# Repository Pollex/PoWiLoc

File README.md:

# PoWiLoc
Pollex' Wireless Locator (PoWi Locator) is a fully Open-Source device used to test LoRaWAN connections and map them on the PoWi website and/or the [TTN Mapper](https://ttnmapper.org/) website.

The locator is designed to be built by everyone who has some technical knowledge (soldering and programming) and the device has several optional features which can be left out to make assembling the device easier.

The hardware is designed in free and Open-Source software called [KiCAD](https://kicad.org/).

The source code for this device is developed in [Visual Studio Code](https://code.visualstudio.com/) (a lightweight editor) with the [PlatformIO](https://platformio.org/) extension. Also both free and Open-Source. This setup is chosen instead of the Arduino IDE because it allows  for cleaner code and better library management.

## This project is in active development and contributions cannot be received at this point in time. As soon as a minimum viable product is built, contributions will open and links to documentation will be provided.

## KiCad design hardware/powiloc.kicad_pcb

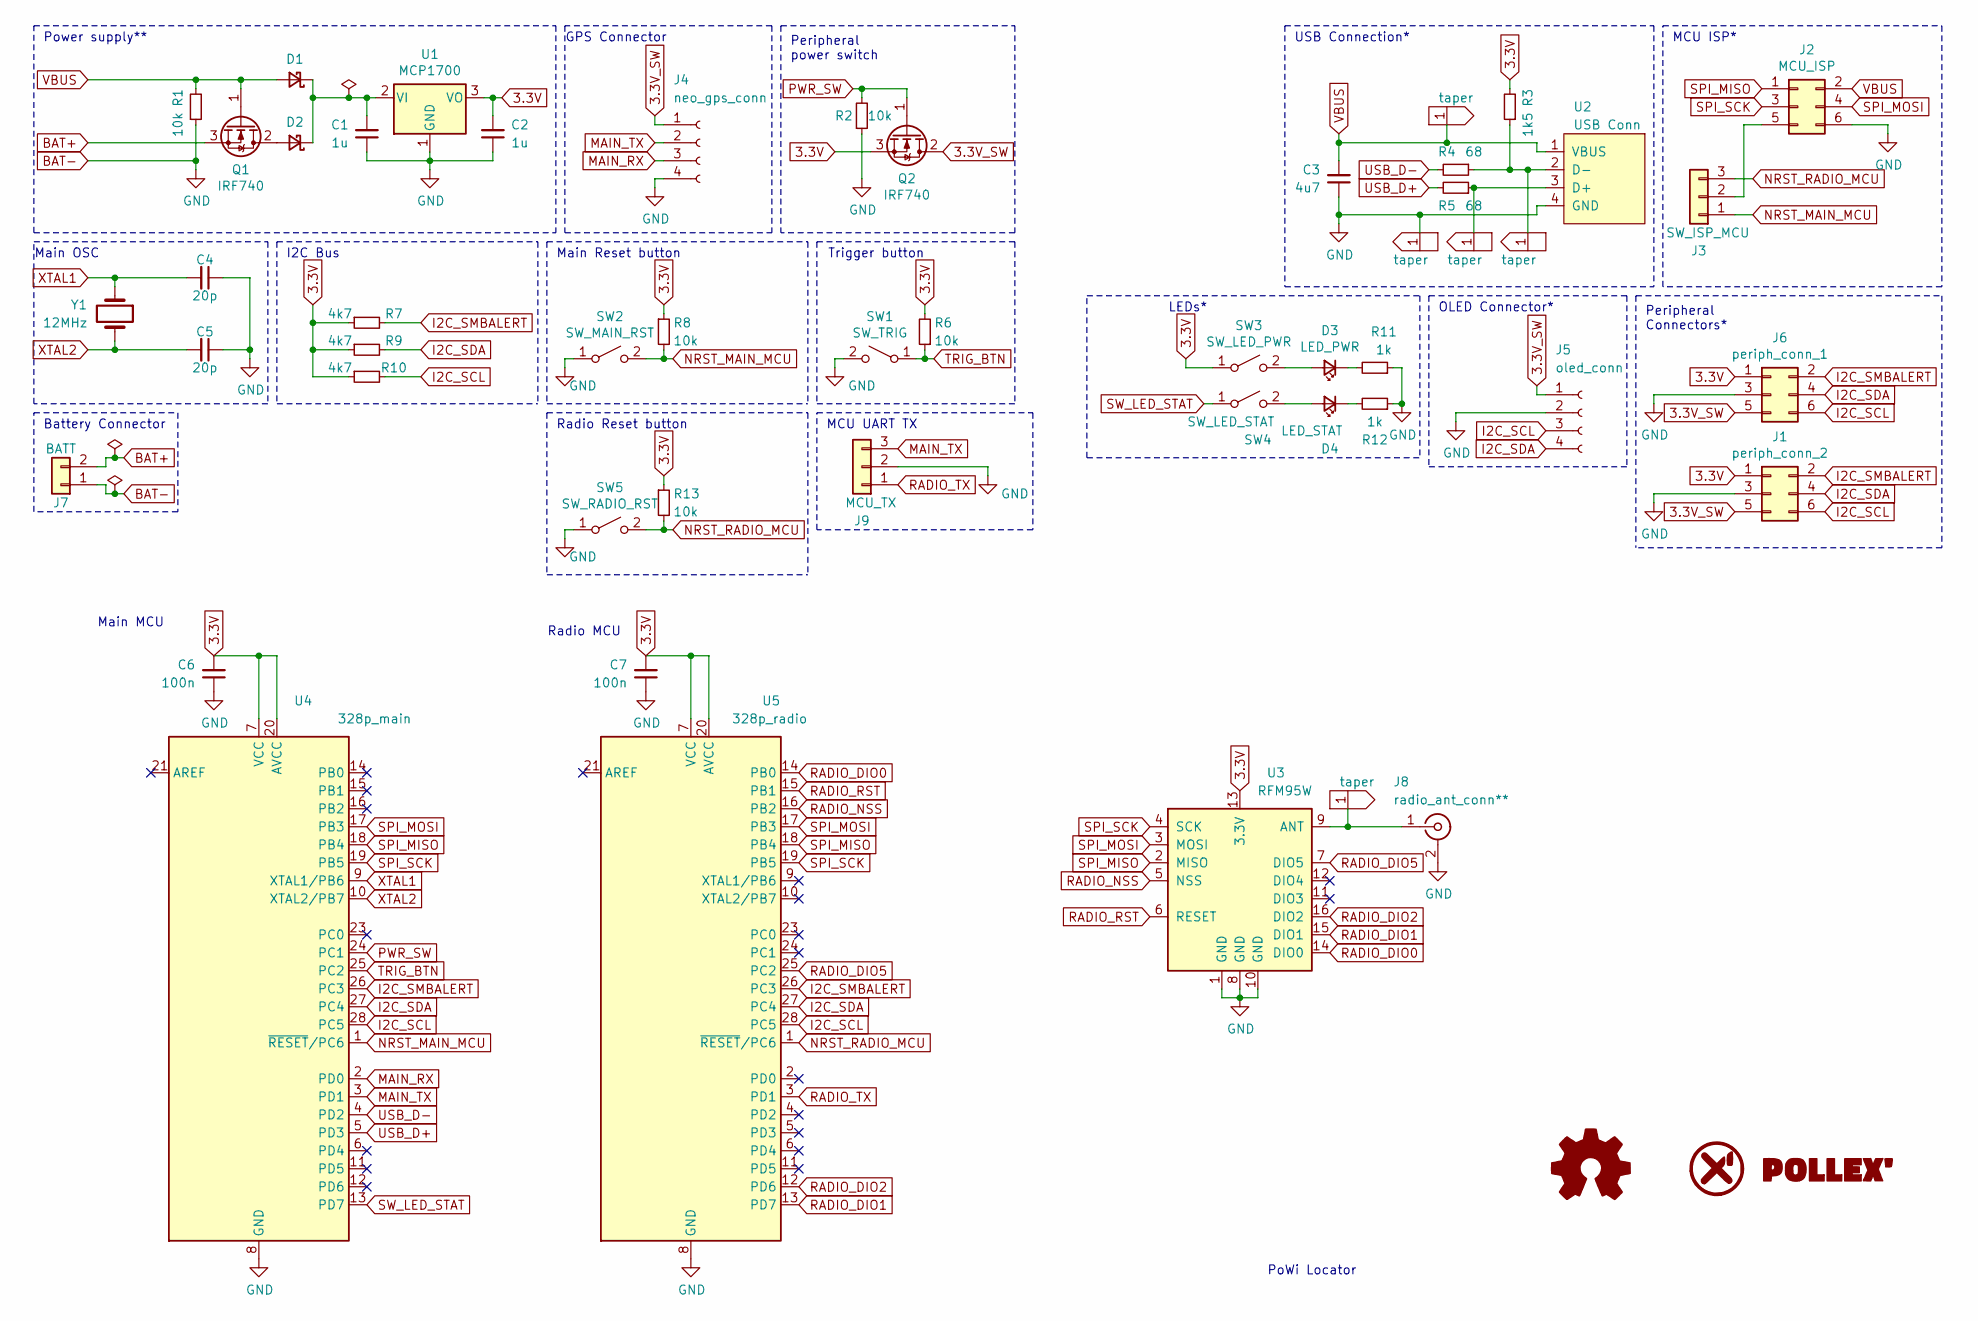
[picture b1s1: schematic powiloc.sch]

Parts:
C1, C2: 1u; C_Disc_D5.0mm_W2.5mm_P5.00mm
C3: 4u7; C_Disc_D5.0mm_W2.5mm_P5.00mm
C4, C5: 20p; C_Disc_D5.0mm_W2.5mm_P2.50mm
C6, C7: 100n; C_Disc_D5.0mm_W2.5mm_P2.50mm
D1, D2: D_Schottky_Small; D_DO-41_SOD81_P7.62mm_Horizontal
D3: LED_PWR; LED_D5.0mm
D4: LED_STAT; LED_D5.0mm
J1: periph_conn_2; PinHeader_2x03_P2.54mm_Vertical
J2: MCU_ISP; PinHeader_2x03_P2.54mm_Vertical
J3: SW_ISP_MCU; PinHeader_1x03_P2.54mm_Vertical
J4: neo_gps_conn; PinSocket_1x04_P2.54mm_Vertical
J5: oled_conn; PinSocket_1x04_P2.54mm_Vertical
J6: periph_conn_1; PinHeader_2x03_P2.54mm_Vertical
J7: BATT; JST_XH_B2B-XH-A_1x02_P2.50mm_Vertical
J8: radio_ant_conn**; SMA_Amphenol_132289_EdgeMount
J9: MCU_TX; PinSocket_1x03_P2.54mm_Vertical
Q1, Q2: IRF740; TO-220-3_Horizontal_TabDown
R1, R2, R6, R8, R13: 10k; R_Axial_DIN0207_L6.3mm_D2.5mm_P7.62mm_Horizontal
R3: 1k5; R_Axial_DIN0207_L6.3mm_D2.5mm_P7.62mm_Horizontal
R4, R5: 68; R_Axial_DIN0207_L6.3mm_D2.5mm_P7.62mm_Horizontal
R7, R9, R10: 4k7; R_Axial_DIN0207_L6.3mm_D2.5mm_P7.62mm_Horizontal
R11, R12: 1k; R_Axial_DIN0207_L6.3mm_D2.5mm_P7.62mm_Horizontal
SW1: SW_TRIG; SW_PUSH_6mm
SW2: SW_MAIN_RST; SW_PUSH_6mm
SW3: SW_LED_PWR; PinHeader_1x02_P2.54mm_Vertical
SW4: SW_LED_STAT; PinHeader_1x02_P2.54mm_Vertical
SW5: SW_RADIO_RST; SW_PUSH_6mm
T1, T2, T5: taper; uwT0.50_0.40_1.00_1.46_1.20
T3, T4: taper; uwT0.50_0.15_1.00_1.24_3.00
U1: MCP1700; TO-92_Inline
U2: USB Conn; USBPCB
U3: RFM95W; HOPERF_RFM9XW_SMD
U4: 328p_main; DIP-28_W7.62mm_Socket
U5: 328p_radio; DIP-28_W7.62mm_Socket
Y1: 12MHz; Crystal_HC49-U_Vertical

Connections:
3.3V: C2.2, C6.2, C7.2, J1.1, J6.1, Q2.3 (S), R3.2, R6.2, R7.1, R8.1, R9.1, R10.1, R13.1, SW3.1 (A), U1.3 (VO), U3.13 (3.3V), U4.7 (VCC), U4.20 (AVCC), U5.7 (VCC), U5.20 (AVCC)
3.3V_SW: J1.5, J4.1, J5.1, J6.5, Q2.2 (D)
BAT+: J7.2, Q1.3 (S)
BAT-: C1.1, C2.1, C3.1, C4.1, C5.1, C6.1, C7.1, J1.3, J2.6, J4.4, J5.2, J6.3, J7.1, J8.2 (Ext), J9.2, R1.1, R2.1, R11.1, R12.1, SW1.2 (B), SW2.1 (A), SW5.1 (A), T2.1, U1.1 (GND), U2.4 (GND), U3.1 (GND), U3.8 (GND), U3.10 (GND), U4.8 (GND), U4.22 (GND), U5.8 (GND), U5.22 (GND)
I2C_SCL: J1.6, J5.3, J6.6, R10.2, U4.28 (PC5), U5.28 (PC5)
I2C_SDA: J1.4, J5.4, J6.4, R9.2, U4.27 (PC4), U5.27 (PC4)
I2C_SMBALERT: J1.2, J6.2, R7.2, U4.26 (PC3), U5.26 (PC3)
MAIN_RX: J4.3, U4.2 (PD0)
MAIN_TX: J4.2, J9.3, U4.3 (PD1)
NRST_MAIN_MCU: J3.1, R8.2, SW2.2 (B), U4.1 (~RESET~/PC6)
NRST_RADIO_MCU: J3.3, R13.2, SW5.2 (B), U5.1 (~RESET~/PC6)
unnamed: C1.2, D1.1 (K), D2.1 (K), U1.2 (VI)
unnamed: D2.2 (A), Q1.2 (D)
unnamed: D3.1 (K), R11.2
unnamed: D3.2 (A), SW3.2 (B)
unnamed: D4.1 (K), R12.2
unnamed: D4.2 (A), SW4.2 (B)
unnamed: J2.5, J3.2
unnamed: J8.1 (In), T5.1, U3.9 (ANT)
unnamed: R3.1, R4.1, T4.1, U2.2 (D-)
unnamed: R5.1, T3.1, U2.3 (D+)
PWR_SW: Q2.1 (G), R2.2, U4.24 (PC1)
RADIO_DIO0: U3.14 (DIO0), U5.14 (PB0)
RADIO_DIO1: U3.15 (DIO1), U5.13 (PD7)
RADIO_DIO2: U3.16 (DIO2), U5.12 (PD6)
RADIO_DIO5: U3.7 (DIO5), U5.25 (PC2)
RADIO_NSS: U3.5 (NSS), U5.16 (PB2)
RADIO_RST: U3.6 (RESET), U5.15 (PB1)
RADIO_TX: J9.1, U5.3 (PD1)
SPI_MISO: J2.1, U3.2 (MISO), U4.18 (PB4), U5.18 (PB4)
SPI_MOSI: J2.4, U3.3 (MOSI), U4.17 (PB3), U5.17 (PB3)
SPI_SCK: J2.3, U3.4 (SCK), U4.19 (PB5), U5.19 (PB5)
SW_LED_STAT: SW4.1 (A), U4.13 (PD7)
TRIG_BTN: R6.1, SW1.1 (A), U4.25 (PC2)
USB_D+: R5.2, U4.5 (PD3)
USB_D-: R4.2, U4.4 (PD2)
VBUS: C3.2, D1.2 (A), J2.2, Q1.1 (G), R1.2, T1.1, U2.1 (VBUS)
XTAL1: C4.2, U4.9 (XTAL1/PB6), Y1.1
XTAL2: C5.2, U4.10 (XTAL2/PB7), Y1.2

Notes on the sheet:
Main OSC
Main MCU
Main Reset button
PoWi Locator
USB Connection*
Power supply**
MCU ISP*
GPS Connector
OLED Connector*
Trigger button
Radio MCU
I2C Bus
Peripheral power switch
LEDs*
Peripheral Connectors*
Battery Connector
Radio Reset button
MCU UART TX

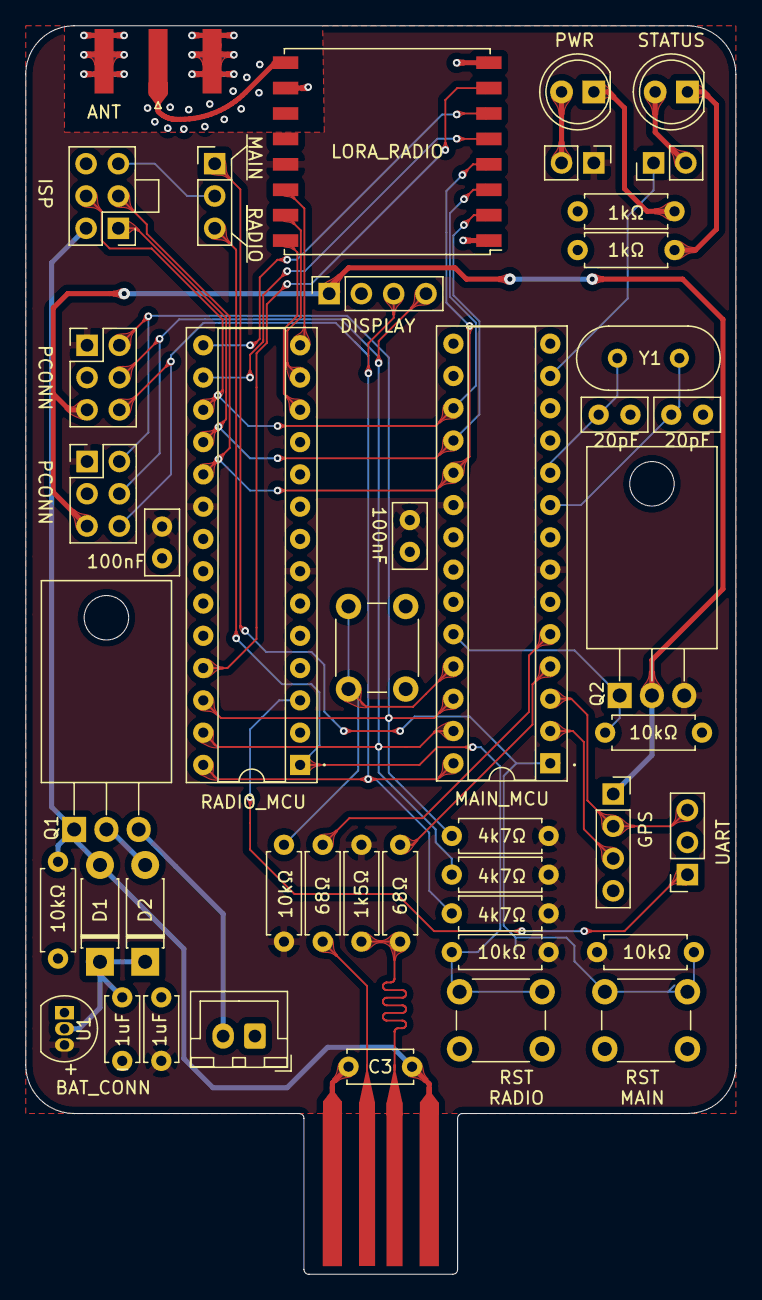
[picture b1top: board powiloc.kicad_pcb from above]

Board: 2 copper layers, 55.9 x 98.2 mm, 51 parts (0 on the bottom side), 39 nets.

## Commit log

2021-01-23 Add hardware files
2021-01-23 Create firmware folder for main and radio
2021-01-23 Use single platformio.ini for both MCUs
2021-01-23 Keep lib,include
2021-01-26 Update schematic design
2021-01-26 PCB Placement
2021-01-29 Corrupt save
2021-01-29 Use relative lib
2021-02-06 Add WIP libs
2021-02-25 Update production
